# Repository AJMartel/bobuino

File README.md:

[:fr:](LISEZMOI.md) [:uk:](README.md)

# bobuino
atmega 1284 arduino compatible

design inspired of [Croos Road Fencing Center](http://www.crossroadsfencing.com/BobuinoRev17/) work

features:

- microSD card
- lcd display 82x48 pixels
- rotary encoder
- wifi esp8266

## Revisions

rev1 (/v1backup)
- U5 vcc and gnd are inverted !!!

- D1 & D2 light when inactive
- 1n4148 is missing between vcc and rst

rev2 
- correct connection for U5, D1, D2 and D5

## How to install MightyCore
#### Boards Manager Installation
This installation method requires Arduino IDE version 1.6.4 or greater.
* Open the Arduino IDE.
* Open the **File > Preferences** menu item.
* Enter the following URL in **Additional Boards Manager URLs**: `https://mcudude.github.io/MightyCore/package_MCUdude_MightyCore_index.json`
  * Separate the URLs using a comma ( **,** ) if you have more than one URL
* Open the **Tools > Board > Boards Manager...** menu item.
* Wait for the platform indexes to finish downloading.
* Scroll down until you see the **MightyCore** entry and click on it.
* Click **Install**.
* After installation is complete close the **Boards Manager** window.

#### Manual Installation
On https://github.com/MCUdude/MightyCore , 
Click on the "Download ZIP" button. Extract the ZIP file, and move the extracted folder to the location "**~/Documents/Arduino/hardware**". Create the "hardware" folder if it doesn't exist.
Open Arduino IDE, and a new category in the boards menu called "MightyCore" will show up.

### Configuration

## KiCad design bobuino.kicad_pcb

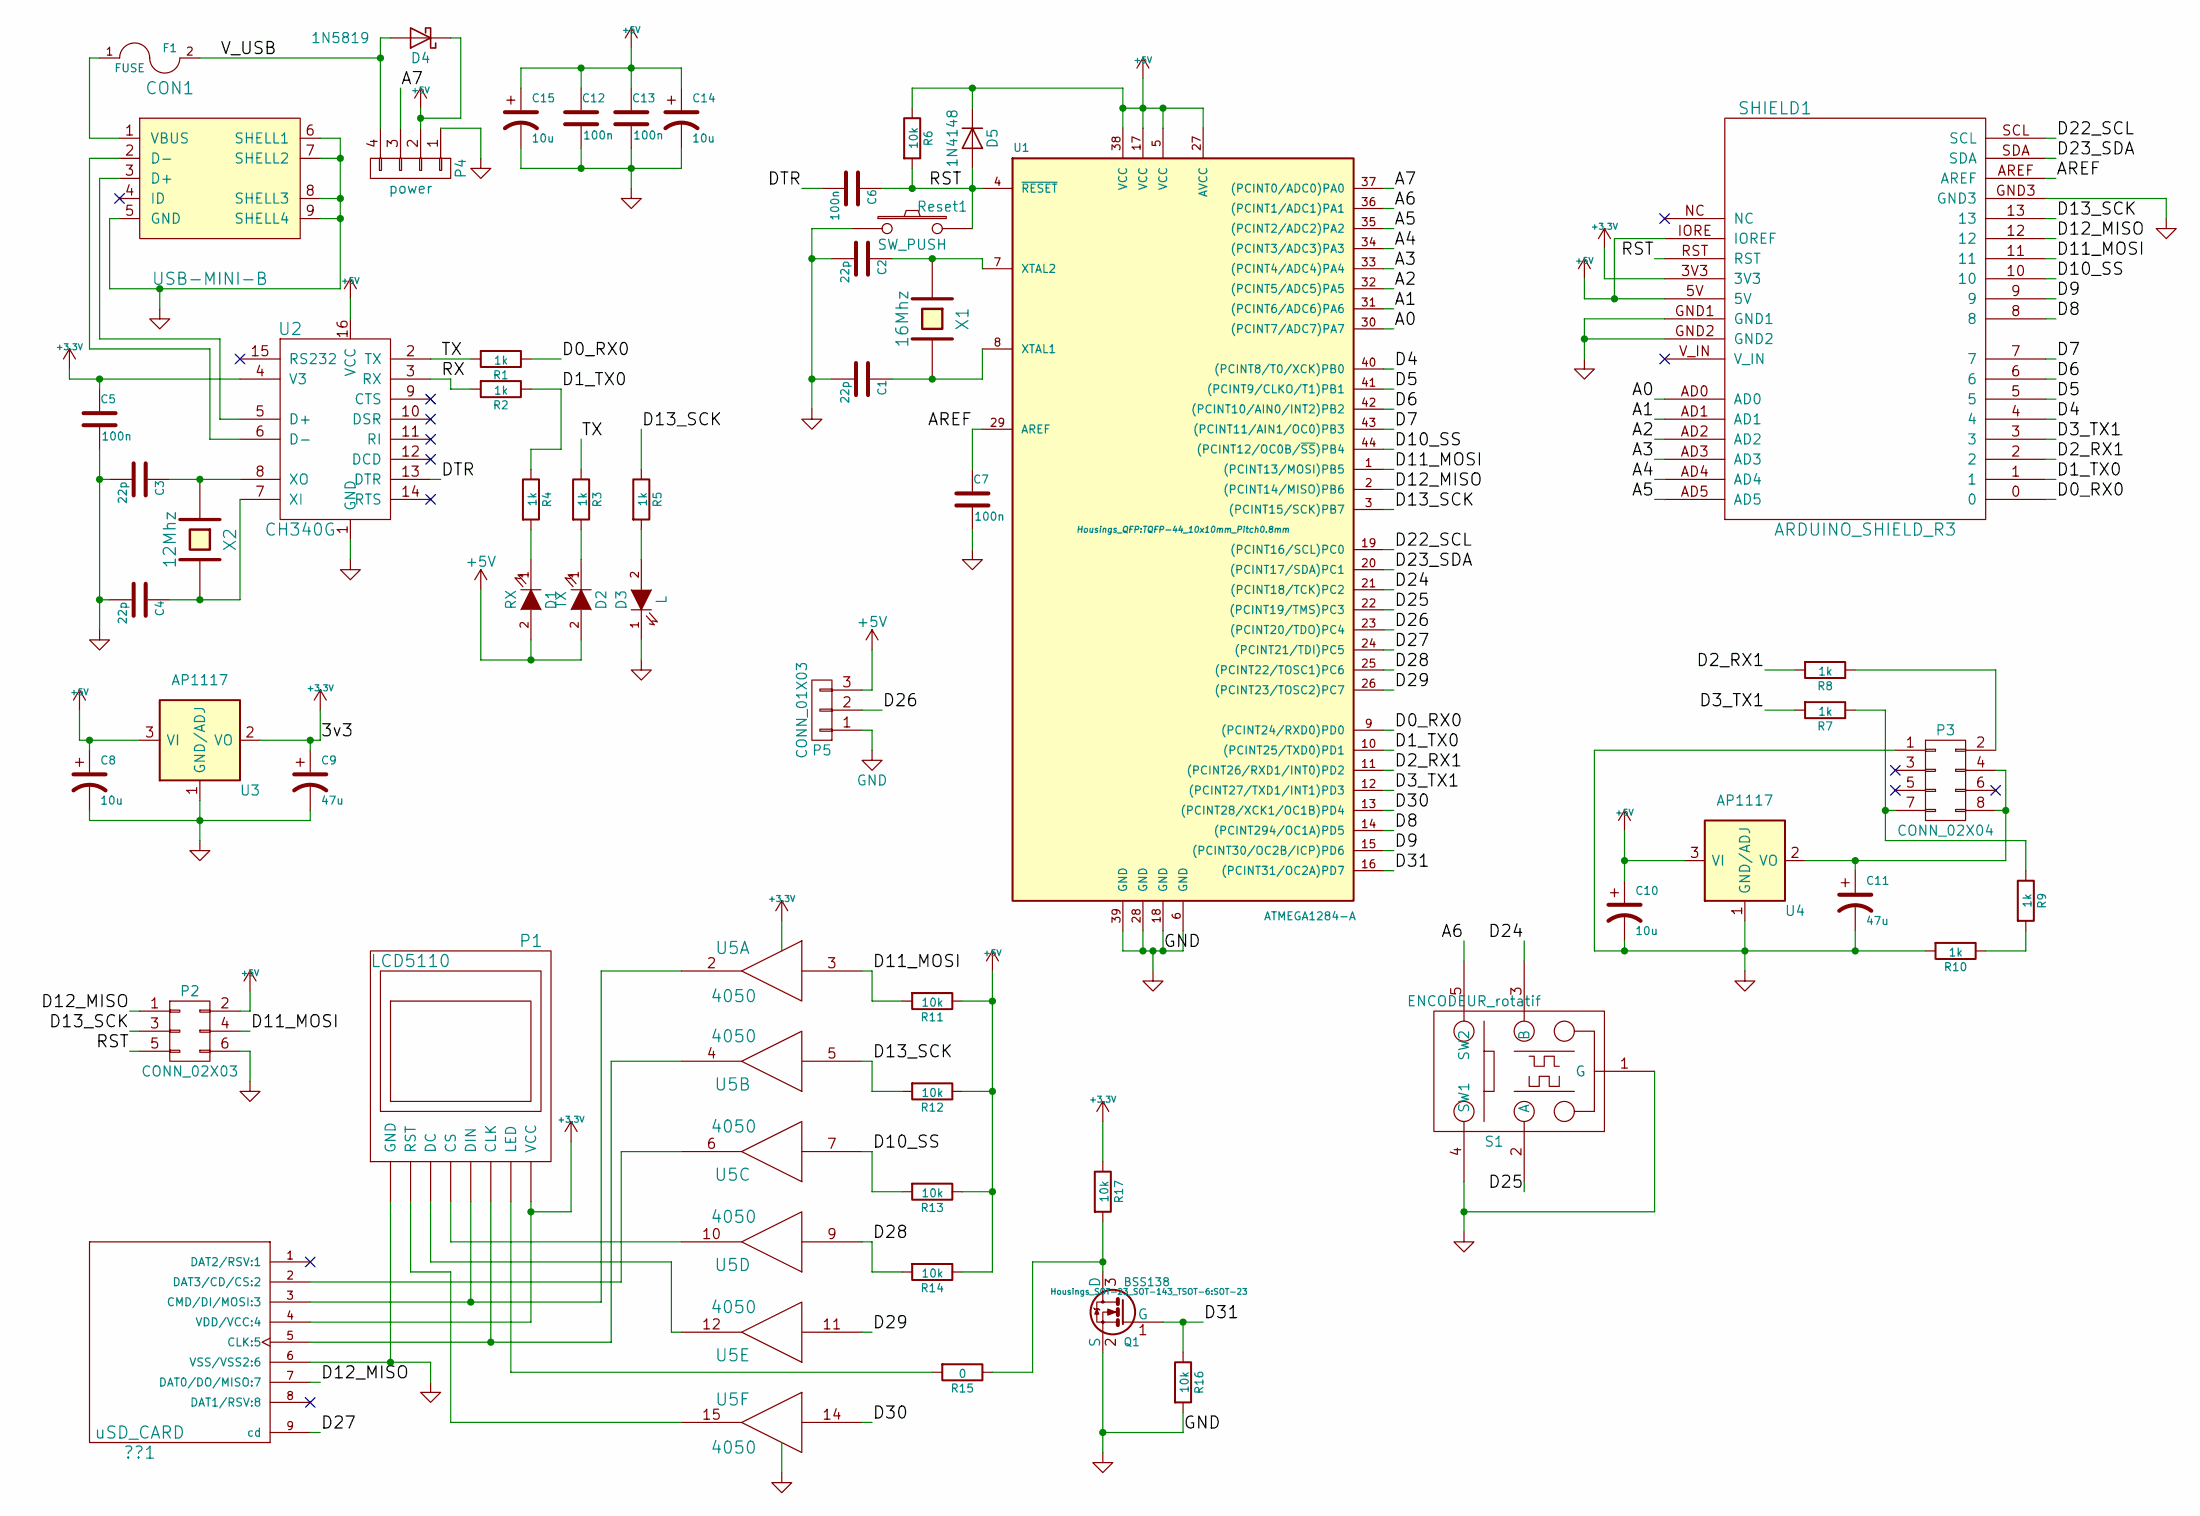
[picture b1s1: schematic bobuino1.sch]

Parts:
??1: uSD_CARD; MicroSD_alliexpress
C1, C2, C3, C4: 22p; C_0805
C5, C6, C7, C12, C13: 100n; C_0805
C8, C10, C14, C15: 10u; TantalC_SizeA_EIA-3216_Reflow
C9, C11: 47u; TantalC_SizeB_EIA-3528_Reflow
CON1: USB-MINI-B; USB_Mini-B
D1: RX; LED-0805
D2: TX; LED-0805
D3: L; LED-0805
D4: 1N5819; Diode-SMA_Standard
D5: 1N4148; SOD-123
F1: FUSE; Fuse_SMD1206_Reflow
P1: LCD5110; LCD5110_ali
P2: CONN_02X03; Pin_Header_Straight_2x03
P3: CONN_02X04; Pin_Header_Straight_2x04
P4: power; Socket_Strip_Straight_1x04
P5: CONN_01X03; Pin_Header_Straight_1x03
Q1: BSS138; SOT-23
R1, R2, R3, R4, R5, R7, R8, R9, R10: 1k; R_0805
R6, R11, R12, R13, R14, R16, R17: 10k; R_0805
R15: 0; R_0805
Reset1: SW_PUSH; SW_SPST_PTS645
S1: ENCODEUR_rotatif
SHIELD1: ARDUINO_SHIELD_R3
U1: ATMEGA1284-A; TQFP-44_10x10mm_Pitch0.8mm
U2: CH340G; SO-16-N
U3, U4: AP1117; SOT-223
U5: 4050; SO-16-N
X1: 16Mhz; Crystal_HC49-U_Vertical
X2: 12Mhz; Crystal_HC49-U_Vertical

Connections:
+3V3: ??1.4 (VDD/VCC:4), C5.1, C9.1, P1.VCC, R17.1, SHIELD1.3V3, U2.4 (V3), U3.2 (VO), U3.4 (VO), U5.1 (VCC)
+5V: C8.1, C10.1, C12.1, C13.1, C14.1, C15.1, D1.2 (A), D2.2 (A), D4.1 (K), D5.1 (K), P2.2, P4.2, P5.3, R6.1, R11.1, R12.1, R13.1, R14.1, SHIELD1.5V, SHIELD1.IORE (IOREF), U1.5 (VCC), U1.17 (VCC), U1.27 (AVCC), U1.38 (VCC), U2.16 (VCC), U3.3 (VI), U4.3 (VI)
/bobuino1/A0: SHIELD1.AD0, U1.30 ((PCINT7/ADC7)PA7)
/bobuino1/A1: SHIELD1.AD1, U1.31 ((PCINT6/ADC6)PA6)
/bobuino1/A2: SHIELD1.AD2, U1.32 ((PCINT5/ADC5)PA5)
/bobuino1/A3: SHIELD1.AD3, U1.33 ((PCINT4/ADC4)PA4)
/bobuino1/A4: SHIELD1.AD4, U1.34 ((PCINT3/ADC3)PA3)
/bobuino1/A5: SHIELD1.AD5, U1.35 ((PCINT2/ADC2)PA2)
/bobuino1/A6: S1.5 (SW2), U1.36 ((PCINT1/ADC1)PA1)
/bobuino1/A7: P4.3, U1.37 ((PCINT0/ADC0)PA0)
/bobuino1/AREF: C7.1, SHIELD1.AREF, U1.29 (AREF)
/bobuino1/D0_RX0: R1.1, SHIELD1.0, U1.9 ((PCINT24/RXD0)PD0)
/bobuino1/D1_TX0: R2.1, R4.1, SHIELD1.1, U1.10 ((PCINT25/TXD0)PD1)
/bobuino1/D2_RX1: R8.2, SHIELD1.2, U1.11 ((PCINT26/RXD1/INT0)PD2)
/bobuino1/D3_TX1: R7.2, SHIELD1.3, U1.12 ((PCINT27/TXD1/INT1)PD3)
/bobuino1/D4: SHIELD1.4, U1.40 ((PCINT8/T0/XCK)PB0)
/bobuino1/D5: SHIELD1.5, U1.41 ((PCINT9/CLKO/T1)PB1)
/bobuino1/D6: SHIELD1.6, U1.42 ((PCINT10/AIN0/INT2)PB2)
/bobuino1/D7: SHIELD1.7, U1.43 ((PCINT11/AIN1/OC0)PB3)
/bobuino1/D8: SHIELD1.8, U1.14 ((PCINT294/OC1A)PD5)
/bobuino1/D9: SHIELD1.9, U1.15 ((PCINT30/OC2B/ICP)PD6)
/bobuino1/D10_SS: R13.2, SHIELD1.10, U1.44 ((PCINT12/OC0B/~SS~)PB4), U5.7
/bobuino1/D11_MOSI: P2.4, R11.2, SHIELD1.11, U1.1 ((PCINT13/MOSI)PB5), U5.3
/bobuino1/D12_MISO: ??1.7 (DAT0/DO/MISO:7), P2.1, SHIELD1.12, U1.2 ((PCINT14/MISO)PB6)
/bobuino1/D13_SCK: P2.3, R5.1, R12.2, SHIELD1.13, U1.3 ((PCINT15/SCK)PB7), U5.5
/bobuino1/D22_SCL: SHIELD1.SCL, U1.19 ((PCINT16/SCL)PC0)
/bobuino1/D23_SDA: SHIELD1.SDA, U1.20 ((PCINT17/SDA)PC1)
/bobuino1/D24: S1.3 (B), U1.21 ((PCINT18/TCK)PC2)
/bobuino1/D25: S1.2 (A), U1.22 ((PCINT19/TMS)PC3)
/bobuino1/D26: P5.2, U1.23 ((PCINT20/TDO)PC4)
/bobuino1/D27: ??1.9 (cd), U1.24 ((PCINT21/TDI)PC5)
/bobuino1/D28: R14.2, U1.25 ((PCINT22/TOSC1)PC6), U5.9
/bobuino1/D29: U1.26 ((PCINT23/TOSC2)PC7), U5.11
/bobuino1/D30: U1.13 ((PCINT28/XCK1/OC1B)PD4), U5.14
/bobuino1/D31: Q1.1 (G), R16.1, U1.16 ((PCINT31/OC2A)PD7)
/bobuino1/DTR: C6.2, U2.13 (DTR)
/bobuino1/RST: C6.1, D5.2 (A), P2.5, R6.2, Reset1.2, SHIELD1.RST, U1.4 (~RESET)
/bobuino1/RX: R2.2, U2.3 (RX)
/bobuino1/TX: R1.2, R3.1, U2.2 (TX)
/bobuino1/V_USB: D4.2 (A), F1.2, P4.4
GND: ??1.6 (VSS/VSS2:6), C1.2, C2.2, C3.2, C4.2, C5.2, C7.2, C8.2, C9.2, C10.2, C11.2, C12.2, C13.2, C14.2, C15.2, CON1.5 (GND), CON1.6 (SHELL1), CON1.7 (SHELL2), CON1.8 (SHELL3), CON1.9 (SHELL4), D3.1 (K), P1.GND, P2.6, P3.1, P4.1, P5.1, Q1.2 (S), R10.2, R16.2, Reset1.1, S1.1 (G), S1.4 (SW1), SHIELD1.GND1, SHIELD1.GND2, SHIELD1.GND3, U1.6 (GND), U1.18 (GND), U1.28 (GND), U1.39 (GND), U2.1 (GND), U3.1 (GND/ADJ), U4.1 (GND/ADJ), U5.8 (VSS)
unnamed: ??1.2 (DAT3/CD/CS:2), U5.6
unnamed: ??1.3 (CMD/DI/MOSI:3), P1.DIN, U5.2
unnamed: ??1.5 (CLK:5), P1.CLK, U5.4
unnamed: C1.1, U1.8 (XTAL1), X1.2
unnamed: C2.1, U1.7 (XTAL2), X1.1
unnamed: C3.1, U2.8 (XO), X2.1
unnamed: C4.1, U2.7 (XI), X2.2
unnamed: C11.1, P3.4, P3.8, U4.2 (VO), U4.4 (VO)
unnamed: CON1.1 (VBUS), F1.1
unnamed: CON1.2 (D-), U2.6 (D-)
unnamed: CON1.3 (D+), U2.5 (D+)
unnamed: D1.1 (K), R4.2
unnamed: D2.1 (K), R3.2
unnamed: D3.2 (A), R5.2
unnamed: P1.CS, U5.10
unnamed: P1.DC, U5.12
unnamed: P1.LED, R15.2
unnamed: P1.RST, U5.15
unnamed: P3.2, R8.1
unnamed: P3.7, R7.1, R9.1
unnamed: Q1.3 (D), R15.1, R17.2
unnamed: R9.2, R10.1

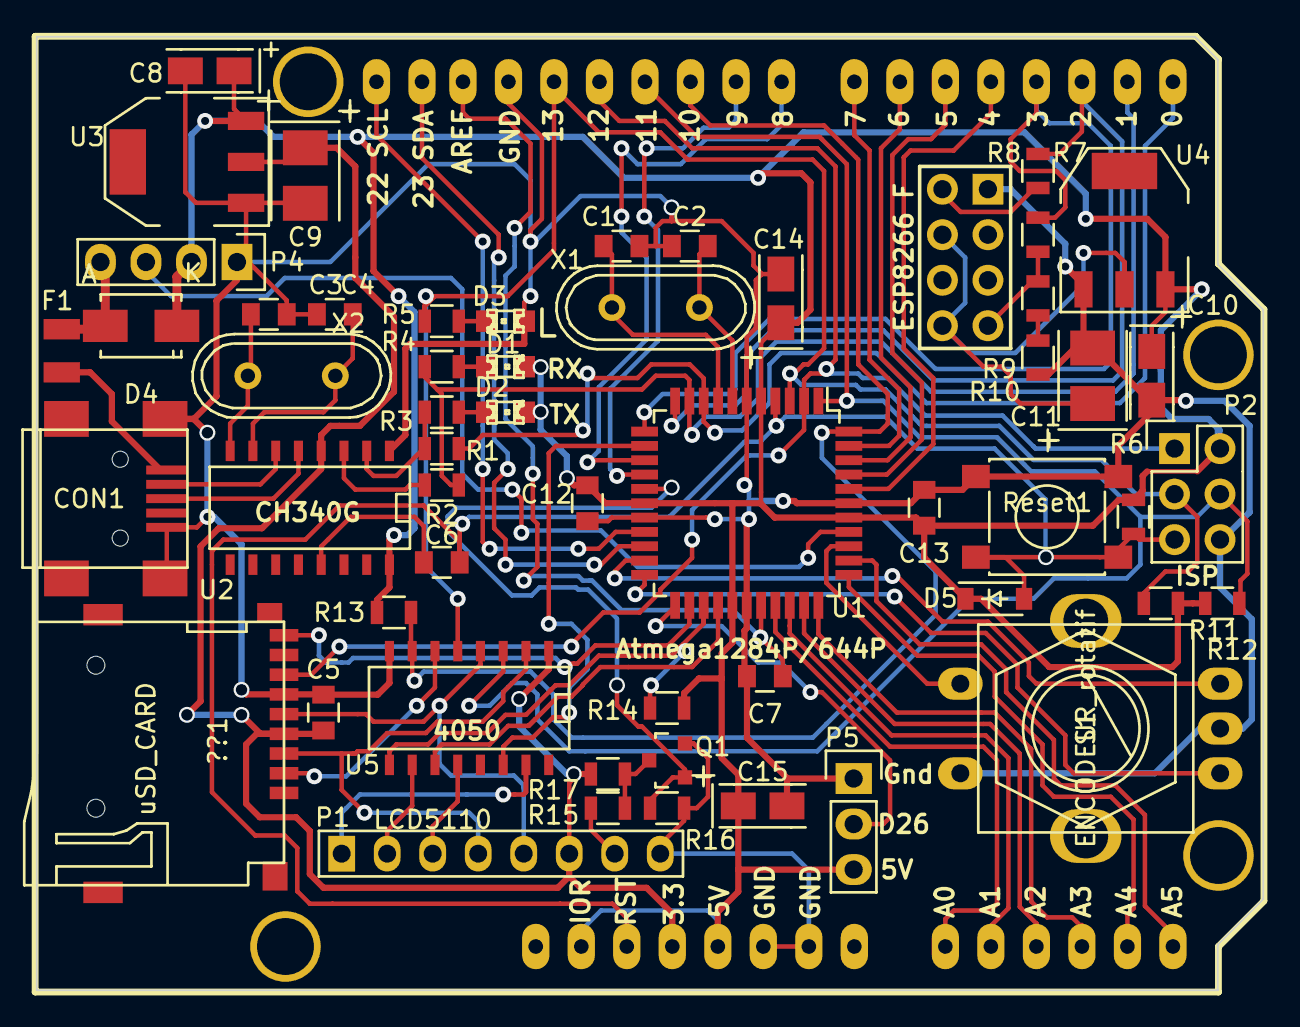
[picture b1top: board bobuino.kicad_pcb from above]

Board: 2 copper layers, 68.5 x 53.2 mm, 56 parts (1 on the bottom side), 63 nets.

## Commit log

2017-09-17 rv1error
